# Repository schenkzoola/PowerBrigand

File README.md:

# PowerBrigand

## About

### How can I get it?

Well, you can build one yourself from the source files here, or better yet, you can join the waitlist for a kit from my Tindie store below:
[https://www.tindie.com/products/schenktronics/power-brigand/](https://www.tindie.com/products/schenktronics/power-brigand/)
The parts for the first batch of kits have been ordered! 

### What is it?

Power Brigand is a module that attaches to HP common slot power supplies that are normally used in servers.  It has connectors and/or binding posts to bring 12v power to your devices.  It also has controls which allow you to turn the power supply on and off, as well as display parameters such as voltage, current, and temperature from the i2c bus on the power supply.

### Why?

After leaving the cryptocurrency mining scene, I had quite a few of these power supplies.  They are plentiful on eBay, and therefore inexpensive.  I felt it wasn't worth my time trying to sell them, and wanted a way to repurpose them.  I was unimpressed with the typical breakout board available from eBay and Aliexpress.

### How?

I found a few resources to start with.  [This one](http://colintd.blogspot.com/2016/10/hacking-hp-common-slot-power-supplies.html) discussed the supply, and compared it to a similar Murata power supply.

The best source of information I found was [this github repo](https://github.com/raplin/DPS-1200FB) where the author, DrTune, reverse engineered a power supply by decompiling the firmware from the internal microcontroller.  DrTune created some sample python code to read and write data to and from the I2C bus.  This gave me information on which registers to query for the data.

Using an arduino nano, a bus pirate, and DrTune's python code as a guide, I was able to successfully read the I2C bus.  This encouraged me to create a PCB with an LCD, output terminals, and fuses.

## Hardware

### Common Slot Power Supply

This is the heart of the Power Brigand, it won't work without one.
There are at least four commonly available versions of these power supplies: 460W, 750W, and two different 1200W versions.

#### 460W

This is the smallest of the power supplies, and the quietest.  Despite its small size, it is capable of producing 38.3A.  My testing has shown that this has the quietest fan, and the most sensitive current measurement capability.

#### 750W

This is the middle size power supply.  It can produce 62.5A.  Its fan is noisier than the 460W, and the minimum current it can accurately display is about 5A.

#### 1200W

There are two 1200W power supplies, one is higher efficiency than the other.  They are sensitive to the input voltage.  At 120V they can only produce 75A. They require a 200V-240V power source to produce their full capability of 100A.  These power supplies also have a minimum accurate current display of about 5A, and they typically have noisier fans than the others.

### Power Brigand

The power brigand consists of a main PCB which integrates the edge card connector, fuses, buttons, LED's, LCD, Arduino Nano, and other supporting components.

#### Fused Outputs

There are three 25A fused outputs, for 75A total output capability.  Each fuse has an LED next to it to indicate whether there is voltage after the fuse.  If one of the LED's is not lit, there is a good chance that fuse is blown.  The fuse holders are designed to accommodate standard automotive blade style fuses.

The outputs can be configured with either binding posts, or Anderson powerpole connectors.  A typical configuration would have two sets of powerpole connectors and one pair of binding posts.

#### Power Button

On the lower left, there is a power button.  Press this button once to turn on the outputs.  Hold this button to turn off the outputs.  The LED next to the power button will illuminate when the outputs are commanded to turn on.

#### LCD and navigation buttons

The LCD is where the information is displayed.  There are four push buttons just below the left of the LCD.  If you see an arrow on the display, it indicates you can push one of these four buttons to navigate.  If you see an arrow pointing up, that means you can press the "up" button.  If you see an arrow pointing to the right, that means you can press the "right" button, and so on.

#### Arduino Nano

The Arduino Nano compatible module is the "brains" of the unit.  It reads the I2C bus on the power supply, commands it on and off, writes data to the LCD, and handles the buttons.  The software is written and C and can easily be modified using the Arduino IDE.

<br />This work is licensed under a <a rel="license" href="http://creativecommons.org/licenses/by-nc-sa/4.0/">Creative Commons Attribution-NonCommercial-ShareAlike 4.0 International License</a>.

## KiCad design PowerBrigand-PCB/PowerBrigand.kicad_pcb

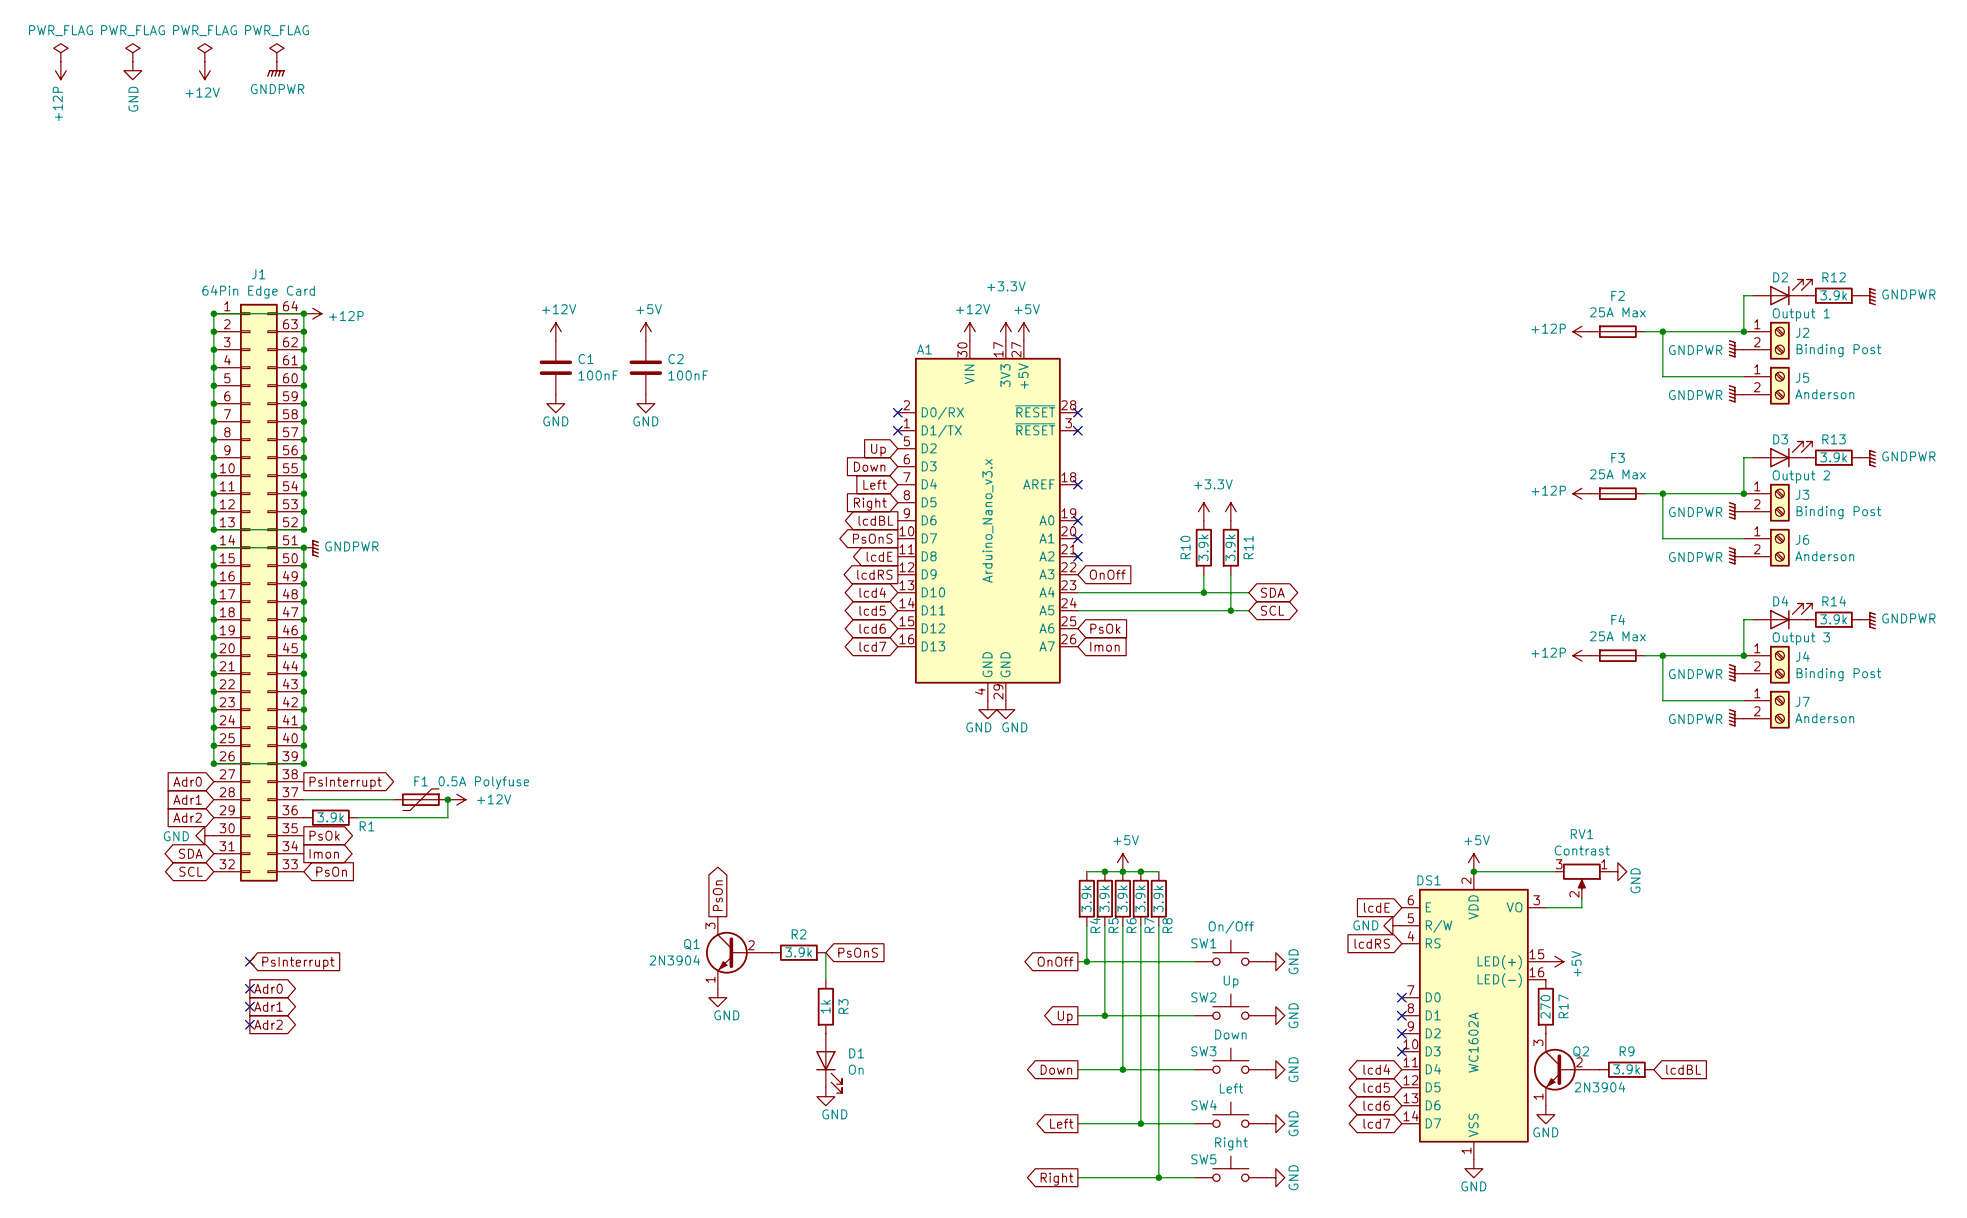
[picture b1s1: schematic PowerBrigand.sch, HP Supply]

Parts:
A1: Arduino_Nano_v3.x; Arduino_Nano
C1, C2: 100nF; C_Disc_D5.0mm_W2.5mm_P5.00mm
D1: On; LED_D5.0mm
D2: Output 1; LED_D5.0mm
D3: Output 2; LED_D5.0mm
D4: Output 3; LED_D5.0mm
DS1: WC1602A; WC1602A_3mmHoles
F1: 0.5A Polyfuse; Fuse_Bourns_MF-RHT100
F2, F3, F4: 25A Max; FuseHolder_Keystone_3557-2
J1: 64Pin Edge Card; FCI_10046971-001LF
J2, J3, J4: Binding Post; BindingPost_Keystone_7019
J5, J6, J7: Anderson; ASMPV45-1X2-RK
Q1, Q2: 2N3904; TO-92_Inline_Wide
R1, R2, R4, R5, R6, R7, R8, R9, R10, R11, R12, R13, R14: 3.9k; R_Axial_DIN0207_L6.3mm_D2.5mm_P10.16mm_Horizontal
R3: 1k; R_Axial_DIN0207_L6.3mm_D2.5mm_P10.16mm_Horizontal
R17: 270; R_Axial_DIN0207_L6.3mm_D2.5mm_P10.16mm_Horizontal
RV1: Contrast; Potentiometer_Bourns_3386P_Vertical
SW1: On/Off; SW_PUSH_6mm_H13mm
SW2: Up; SW_PUSH_6mm_H13mm
SW3: Down; SW_PUSH_6mm_H13mm
SW4: Left; SW_PUSH_6mm_H13mm
SW5: Right; SW_PUSH_6mm_H13mm

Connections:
+3V3: A1.17 (3V3), R10.1, R11.1
+5V: A1.27 (+5V), C2.1, DS1.2 (VDD), DS1.15 (LED(+)), R4.1, R5.1, R6.1, R7.1, R8.1, RV1.3
+12P: F2.2, F3.2, F4.2, J1.1, J1.2, J1.3, J1.4, J1.5, J1.6, J1.7, J1.8, J1.9, J1.10, J1.11, J1.12, J1.13, J1.52, J1.53, J1.54, J1.55, J1.56, J1.57, J1.58, J1.59, J1.60, J1.61, J1.62, J1.63, J1.64
+12V: A1.30 (VIN), C1.1, F1.1, R1.1
Adr0: J1.27
Adr1: J1.28
Adr2: J1.29
Down: A1.6 (D3), R6.2, SW3.1
GND: A1.4 (GND), A1.29 (GND), C1.2, C2.2, D1.1 (K), DS1.1 (VSS), DS1.5 (R/W), J1.30, Q1.1 (E), Q2.1 (E), RV1.1, SW1.2, SW2.2, SW3.2, SW4.2, SW5.2
GNDPWR: J1.14, J1.15, J1.16, J1.17, J1.18, J1.19, J1.20, J1.21, J1.22, J1.23, J1.24, J1.25, J1.26, J1.39, J1.40, J1.41, J1.42, J1.43, J1.44, J1.45, J1.46, J1.47, J1.48, J1.49, J1.50, J1.51, J2.2, J3.2, J4.2, J5.2, J6.2, J7.2, R12.2, R13.2, R14.2
Imon: A1.26 (A7), J1.34
Left: A1.7 (D4), R7.2, SW4.1
unnamed: D1.2 (A), R3.2
unnamed: D2.1 (K), R12.1
unnamed: D2.2 (A), F2.1, J2.1, J5.1
unnamed: D3.1 (K), R13.1
unnamed: D3.2 (A), F3.1, J3.1, J6.1
unnamed: D4.1 (K), R14.1
unnamed: D4.2 (A), F4.1, J4.1, J7.1
unnamed: DS1.3 (VO), RV1.2
unnamed: DS1.16 (LED(-)), R17.1
unnamed: F1.2, J1.37
unnamed: J1.36, R1.2
unnamed: Q1.2 (B), R2.1
unnamed: Q2.2 (B), R9.1
unnamed: Q2.3 (C), R17.2
OnOff: A1.22 (A3), R4.2, SW1.1
PsInterrupt: J1.38
PsOk: A1.25 (A6), J1.35
PsOn: J1.33, Q1.3 (C)
PsOnS: A1.10 (D7), R2.2, R3.1
Right: A1.8 (D5), R8.2, SW5.1
SCL: A1.24 (A5), J1.32, R11.2
SDA: A1.23 (A4), J1.31, R10.2
Up: A1.5 (D2), R5.2, SW2.1
lcd4: A1.13 (D10), DS1.11 (D4)
lcd5: A1.14 (D11), DS1.12 (D5)
lcd6: A1.15 (D12), DS1.13 (D6)
lcd7: A1.16 (D13), DS1.14 (D7)
lcdBL: A1.9 (D6), R9.2
lcdE: A1.11 (D8), DS1.6 (E)
lcdRS: A1.12 (D9), DS1.4 (RS)

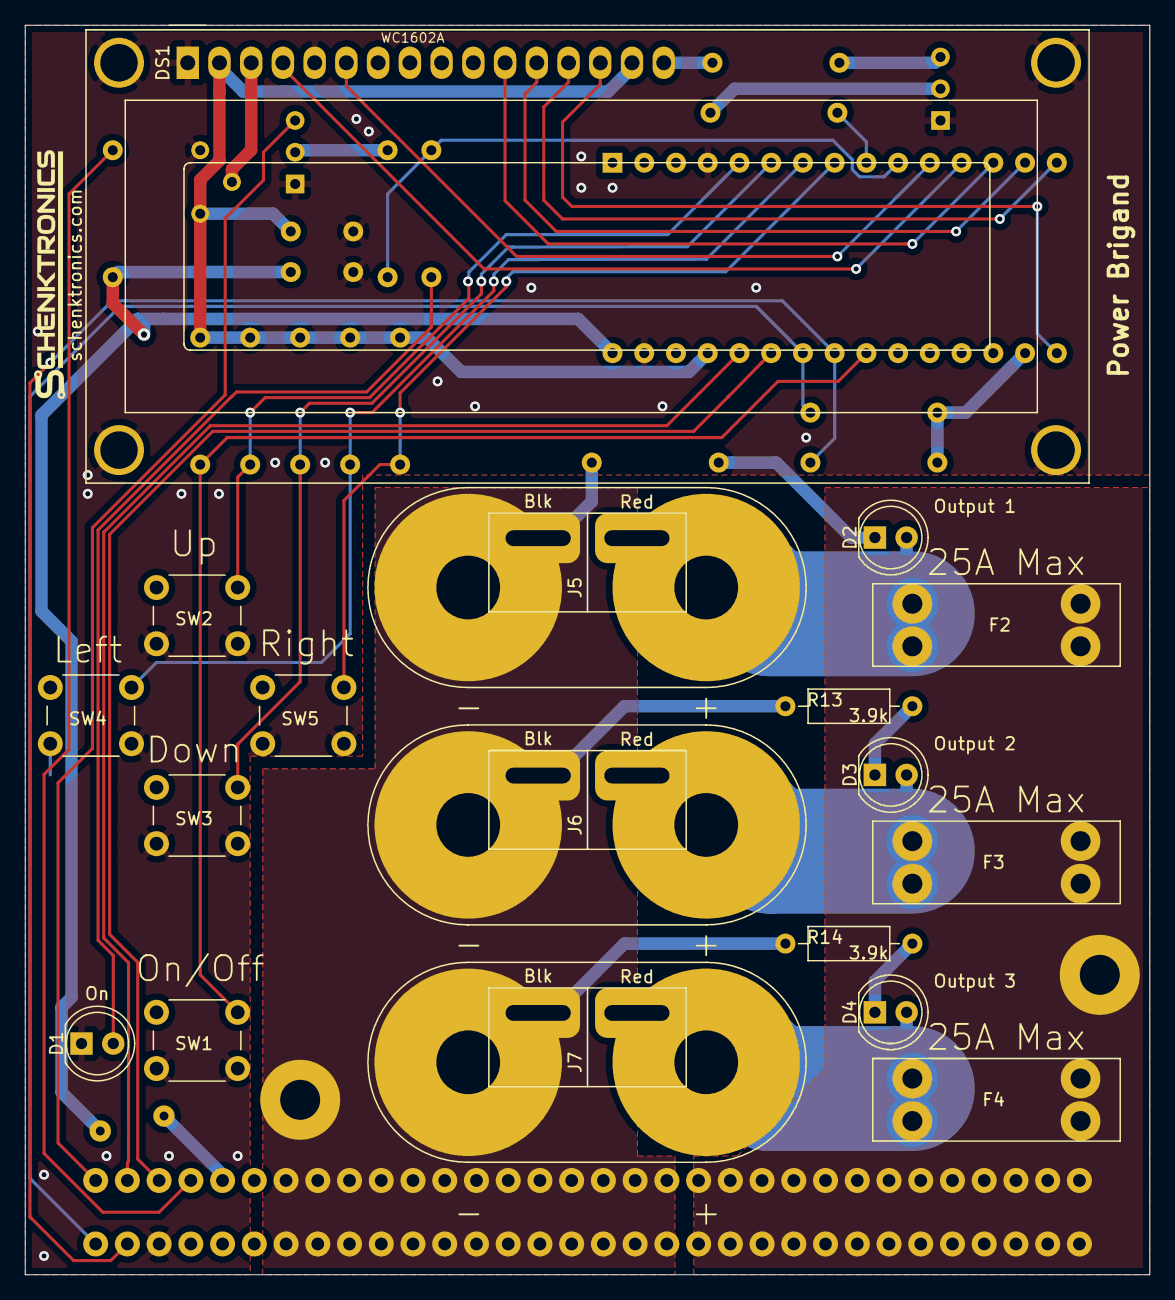
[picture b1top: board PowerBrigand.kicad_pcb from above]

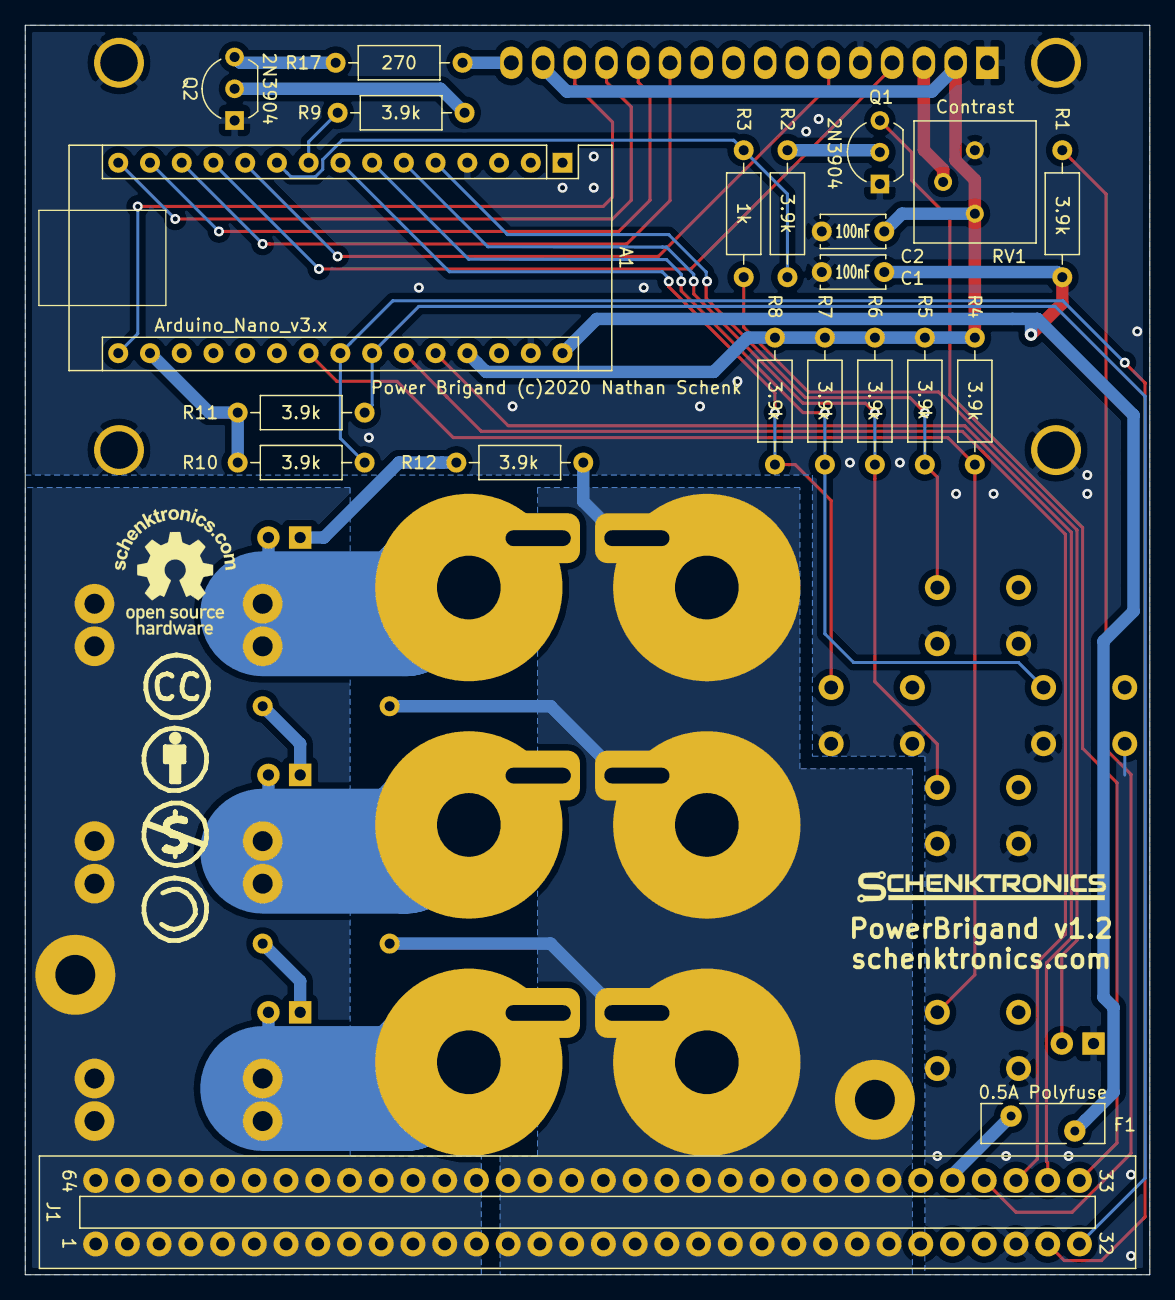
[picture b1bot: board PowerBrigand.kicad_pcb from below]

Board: 2 copper layers, 90.0 x 100.0 mm, 42 parts (21 on the bottom side), 38 nets.

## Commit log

2020-08-08 Add docs
2020-08-08 add software
2020-08-08 add .gitignore
2020-08-08 add case
2020-08-08 add PCB
2020-08-08 add schematic pdf
2020-08-08 update license
2020-08-08 move PCB and schematic .pdf's back into pcb folder
2020-08-08 remove unused function
2020-08-11 Add cropped images without text
2020-08-11 set default power supply type to zero

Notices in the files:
PowerBrigand-PCB/PowerBrigand.kicad_pcb:
(c) 2020
Power Brigand (c)2020 Nathan Schenk
PowerBrigand-PCB/PowerBrigand.sch:
cc-by-nc-sa
